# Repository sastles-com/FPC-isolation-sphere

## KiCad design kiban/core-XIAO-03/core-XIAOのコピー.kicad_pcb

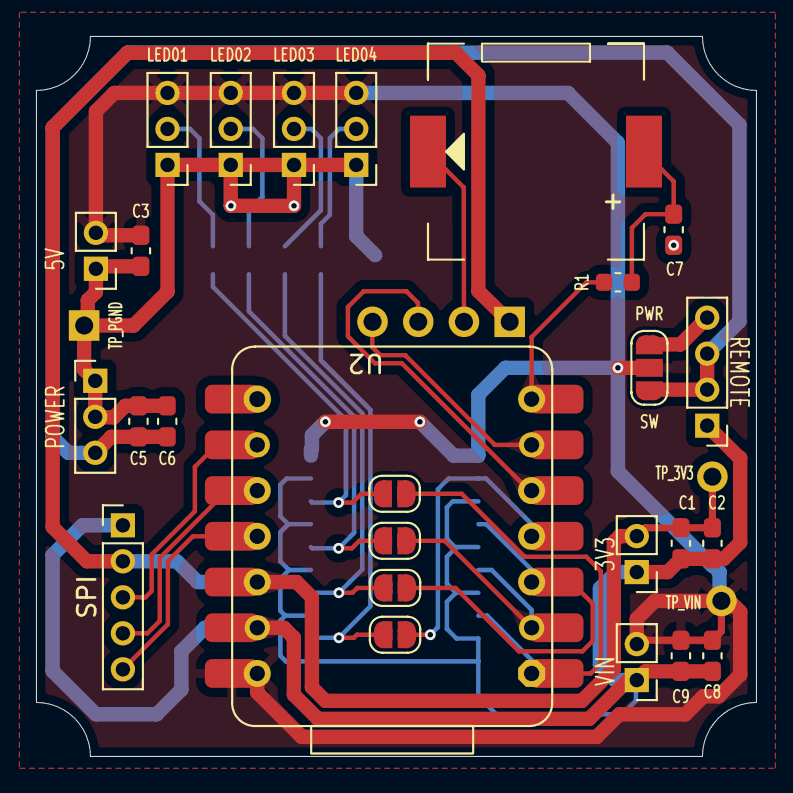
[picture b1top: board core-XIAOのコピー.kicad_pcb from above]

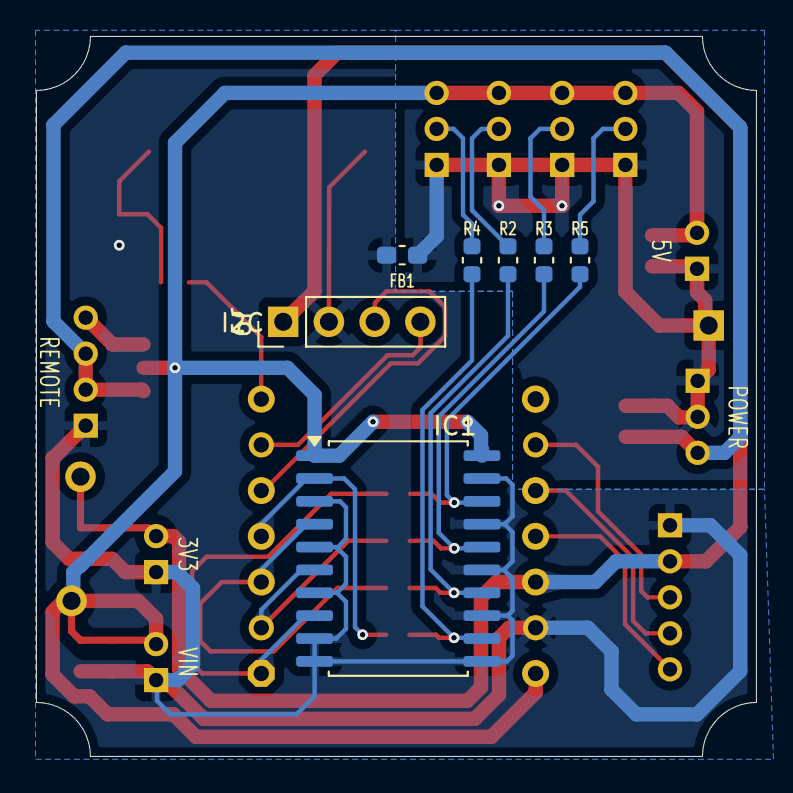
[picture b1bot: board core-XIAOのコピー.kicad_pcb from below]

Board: 2 copper layers, 40.0 x 40.0 mm, 36 parts (7 on the bottom side), 25 nets.

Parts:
C1, C5, C8: 10uF; C_0603_1608Metric_Pad1.08x0.95mm_HandSolder
C2, C3, C6, C7, C9: 0.1uF; C_0603_1608Metric_Pad1.08x0.95mm_HandSolder
FB1: FerriteBead_Small; C_0603_1608Metric_Pad1.08x0.95mm_HandSolder
IC1: 74HCT245; SOIC-20W_7.5x12.8mm_P1.27mm
J1: POWER; PinHeader_1x03_P2.00mm_Vertical
J2: REMOTE; PinHeader_1x04_P2.00mm_Vertical
J3: SPI; PinHeader_1x05_P2.00mm_Vertical
J5: 3V3; PinHeader_1x02_P2.00mm_Vertical
J6: 5V; PinHeader_1x02_P2.00mm_Vertical
J7: LED03; PinHeader_1x03_P2.00mm_Vertical
J8: LED02; PinHeader_1x03_P2.00mm_Vertical
J9: I2C; PinHeader_1x04_P2.54mm_Vertical
J10: LED04; PinHeader_1x03_P2.00mm_Vertical
J11: LED01; PinHeader_1x03_P2.00mm_Vertical
J12: TP_VIN; PinHeader_1x01_P2.54mm_Vertical
J13: TP_3V3; PinHeader_1x01_P2.54mm_Vertical
J14: TP_PGND; PinHeader_1x01_P2.54mm_Vertical
J15: VIN; PinHeader_1x02_P2.00mm_Vertical
JP1: SolderJumper_3_Open; SolderJumper-3_P1.3mm_Open_RoundedPad1.0x1.5mm_NumberLabels
JP2, JP3, JP4, JP5: SolderJumper_2_Open; SolderJumper-2_P1.3mm_Open_RoundedPad1.0x1.5mm
LS1: SPEAKER; speaker-PKLCS1212
R1: 0Ω; C_0603_1608Metric
R2, R3, R4, R5: 33Ω; C_0603_1608Metric
U2: MOUDLE-SEEEDUINO-XIAO-ESP32S3; XIAO-RP2350

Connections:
3V3: C1.1, C2.1, J3.2, J5.2, J9.1, J13.1, U2.12 (3V3)
AGND: C1.2, C2.2, C7.2, C8.2, C9.2, FB1.2, IC1.3 (A2), IC1.5 (A4), IC1.7 (A6), IC1.9 (A8), IC1.10 (GND), IC1.11 (B8), IC1.13 (B6), IC1.15 (B4), IC1.17 (B2), IC1.19 (~OE), J2.1, J3.1, J5.1, J9.2, J15.1, LS1.LEAD-, U2.13 (GND)
GPIO01: IC1.8 (A7), JP2.1 (A), U2.1 (PA02_A0_D0)
GPIO02: IC1.6 (A5), JP3.1 (A), U2.2 (PA4_A1_D1)
GPIO03: IC1.4 (A3), JP4.1 (A), U2.3 (PA10_A2_D2)
GPIO04: IC1.2 (A1), JP5.1 (A), U2.4 (PA11_A3_D3)
GPIO43: R1.1, U2.7 (PB08_A6_TX)
LED01: IC1.18 (B1), JP2.2 (B), R5.2
LED02: IC1.16 (B3), JP3.2 (B), R3.2
LED03: IC1.14 (B5), JP4.2 (B), R2.2
LED04: IC1.12 (B7), JP5.2 (B), R4.2
unnamed: C7.1, LS1.LEAD+, R1.2
unnamed: J2.4, JP1.3 (B)
unnamed: J7.2, R2.1
unnamed: J8.2, R3.1
unnamed: J10.2, R4.1
unnamed: J11.2, R5.1
PGND: C3.2, C5.2, C6.2, FB1.1, J1.1, J1.2, J6.1, J7.1, J8.1, J10.1, J11.1, J14.1
POWER: C5.1, C6.1, J1.3, J2.2, J2.3, JP1.1 (A)
SCL: J9.4, U2.6 (PA9_A5_D5_SCL)
SDA: J9.3, U2.5 (PA8_A4_D4_SDA)
SPI_MISO: J3.4, U2.10 (PA5_A9_D9_MISO)
SPI_MOSI: J3.5, U2.11 (PA6_A10_D10_MOSI)
SPI_SCK: J3.3, U2.9 (PA7_A8_D8_SCK)
VIN: C3.1, C8.1, C9.1, IC1.1 (DIR), IC1.20 (VCC), J6.2, J7.3, J8.3, J10.3, J11.3, J12.1, J15.2, JP1.2 (C), U2.14 (5V)

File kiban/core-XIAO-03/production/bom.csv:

Designator,Footprint,Quantity,Value,LCSC Part #
"C1, C5, C8",0603,3,10uF,
"C2, C3, C6, C7, C9",0603,5,0.1uF,
D1,0603,1,LED,
FB1,0603,1,FerriteBead_Small,
J1,PinHeader_1x03_P2.00mm_Vertical,1,POWER,
J12,PinHeader_1x01_P2.54mm_Vertical,1,TP_VIN,
J13,PinHeader_1x01_P2.54mm_Vertical,1,TP_3V3,
"J14_2, J14",PinHeader_1x01_P2.54mm_Vertical,2,TP_PGND,
J15,PinHeader_1x02_P2.00mm_Vertical,1,VIN,
J2,PinHeader_1x06_P2.54mm_Vertical,1,ESP32-01,
J3,PinHeader_1x05_P2.00mm_Vertical,1,SPI,
J4,PinHeader_1x06_P2.54mm_Vertical,1,ESP32-02,
J5,PinHeader_1x02_P2.00mm_Vertical,1,3V3,
J6,PinHeader_1x02_P2.00mm_Vertical,1,5V,
J9,PinHeader_1x04_P2.54mm_Vertical,1,I2C,
LS1,speaker-PKLCS1212,1,SPEAKER,
R1,0603,1,330Ω,
"R2, R3",0603,2,10kΩ,
U2,XIAO-RP2350,1,MOUDLE-SEEEDUINO-XIAO-ESP32S3,

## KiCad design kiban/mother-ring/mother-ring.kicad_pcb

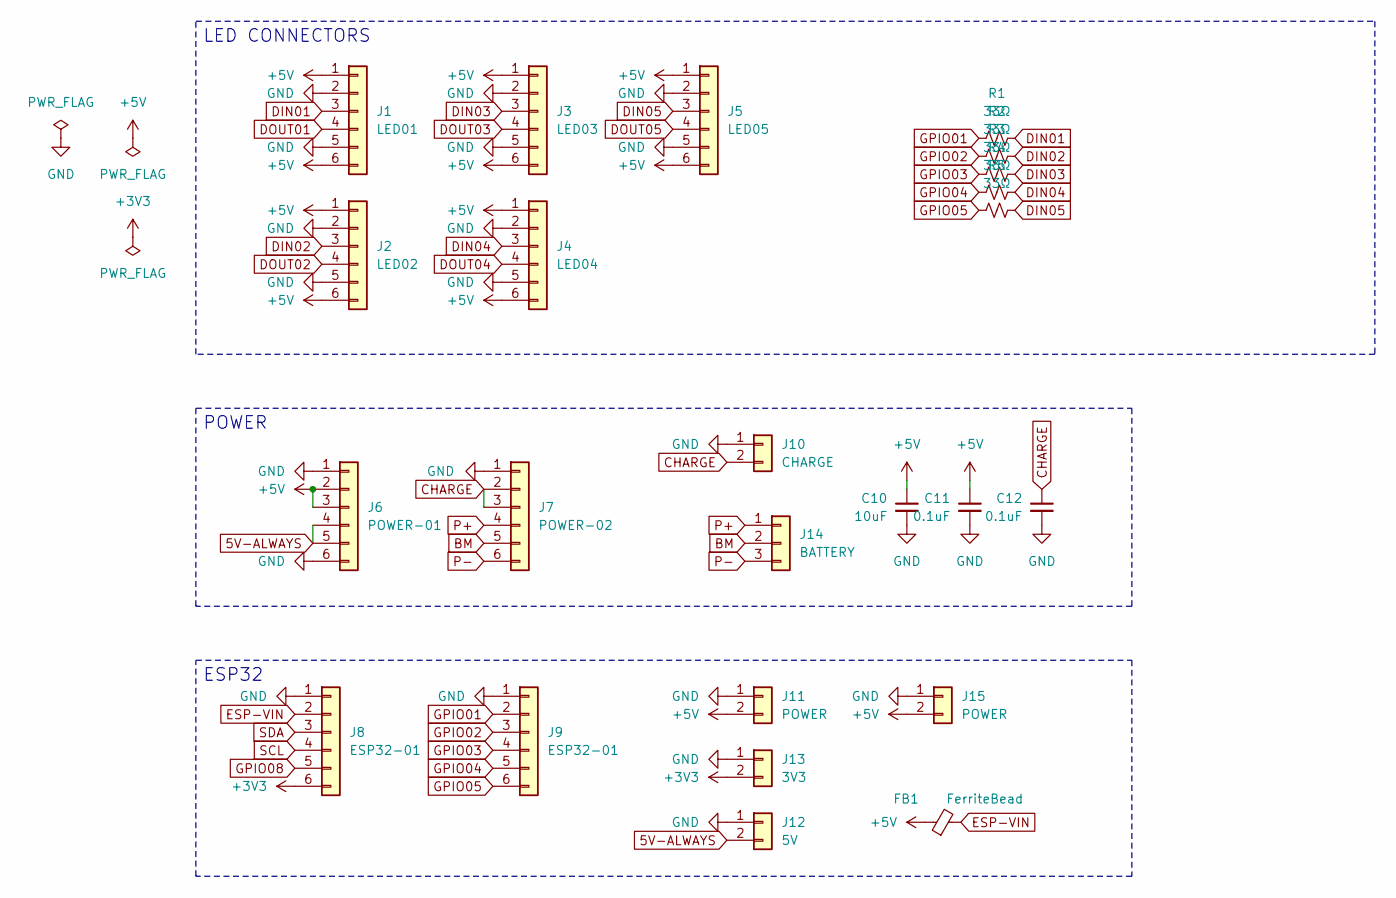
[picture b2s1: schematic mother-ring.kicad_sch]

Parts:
C10: 10uF; C_0603_1608Metric_Pad1.08x0.95mm_HandSolder
C11, C12: 0.1uF; C_0603_1608Metric_Pad1.08x0.95mm_HandSolder
FB1: FerriteBead; L_0603_1608Metric
J1: LED01; pogo-pad 1x06
J2: LED02; pogo-pad 1x06
J3: LED03; pogo-pad 1x06
J4: LED04; pogo-pad 1x06
J5: LED05; pogo-pad 1x06
J6: POWER-01; PinHeader_1x06_P2.54mm_Vertical
J7: POWER-02; PinHeader_1x06_P2.54mm_Vertical
J8, J9: ESP32-01; PinHeader_1x06_P2.54mm_Vertical
J10: CHARGE; PinHeader_1x02_P2.00mm_Vertical
J11, J15: POWER; PinHeader_1x02_P2.00mm_Vertical
J12: 5V; PinHeader_1x02_P2.00mm_Vertical
J13: 3V3; PinHeader_1x02_P2.00mm_Vertical
J14: BATTERY; PinHeader_1x03_P2.00mm_Vertical
R1, R2, R3, R4, R5: 33Ω; R_0603_1608Metric

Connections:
5V-ALWAYS: J6.4, J6.5, J12.2
+3V3: J8.6, J13.2
+5V: C10.1, C11.1, FB1.1, J1.1, J1.6, J2.1, J2.6, J3.1, J3.6, J4.1, J4.6, J5.1, J5.6, J6.2, J6.3, J11.2, J15.2
BM: J7.5, J14.2
CHARGE: C12.1, J7.2, J7.3, J10.2
DIN01: J1.3, R1.2
DIN02: J2.3, R2.2
DIN03: J3.3, R3.2
DIN04: J4.3, R4.2
DIN05: J5.3, R5.2
DOUT01: J1.4
DOUT02: J2.4
DOUT03: J3.4
DOUT04: J4.4
DOUT05: J5.4
ESP-VIN: FB1.2, J8.2
GND: C10.2, C11.2, C12.2, J1.2, J1.5, J2.2, J2.5, J3.2, J3.5, J4.2, J4.5, J5.2, J5.5, J6.1, J6.6, J7.1, J8.1, J9.1, J10.1, J11.1, J12.1, J13.1, J15.1
GPIO01: J9.2, R1.1
GPIO02: J9.3, R2.1
GPIO03: J9.4, R3.1
GPIO04: J9.5, R4.1
GPIO05: J9.6, R5.1
GPIO08: J8.5
P+: J7.4, J14.1
P-: J7.6, J14.3
SCL: J8.4
SDA: J8.3

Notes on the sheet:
POWER
ESP32
LED CONNECTORS

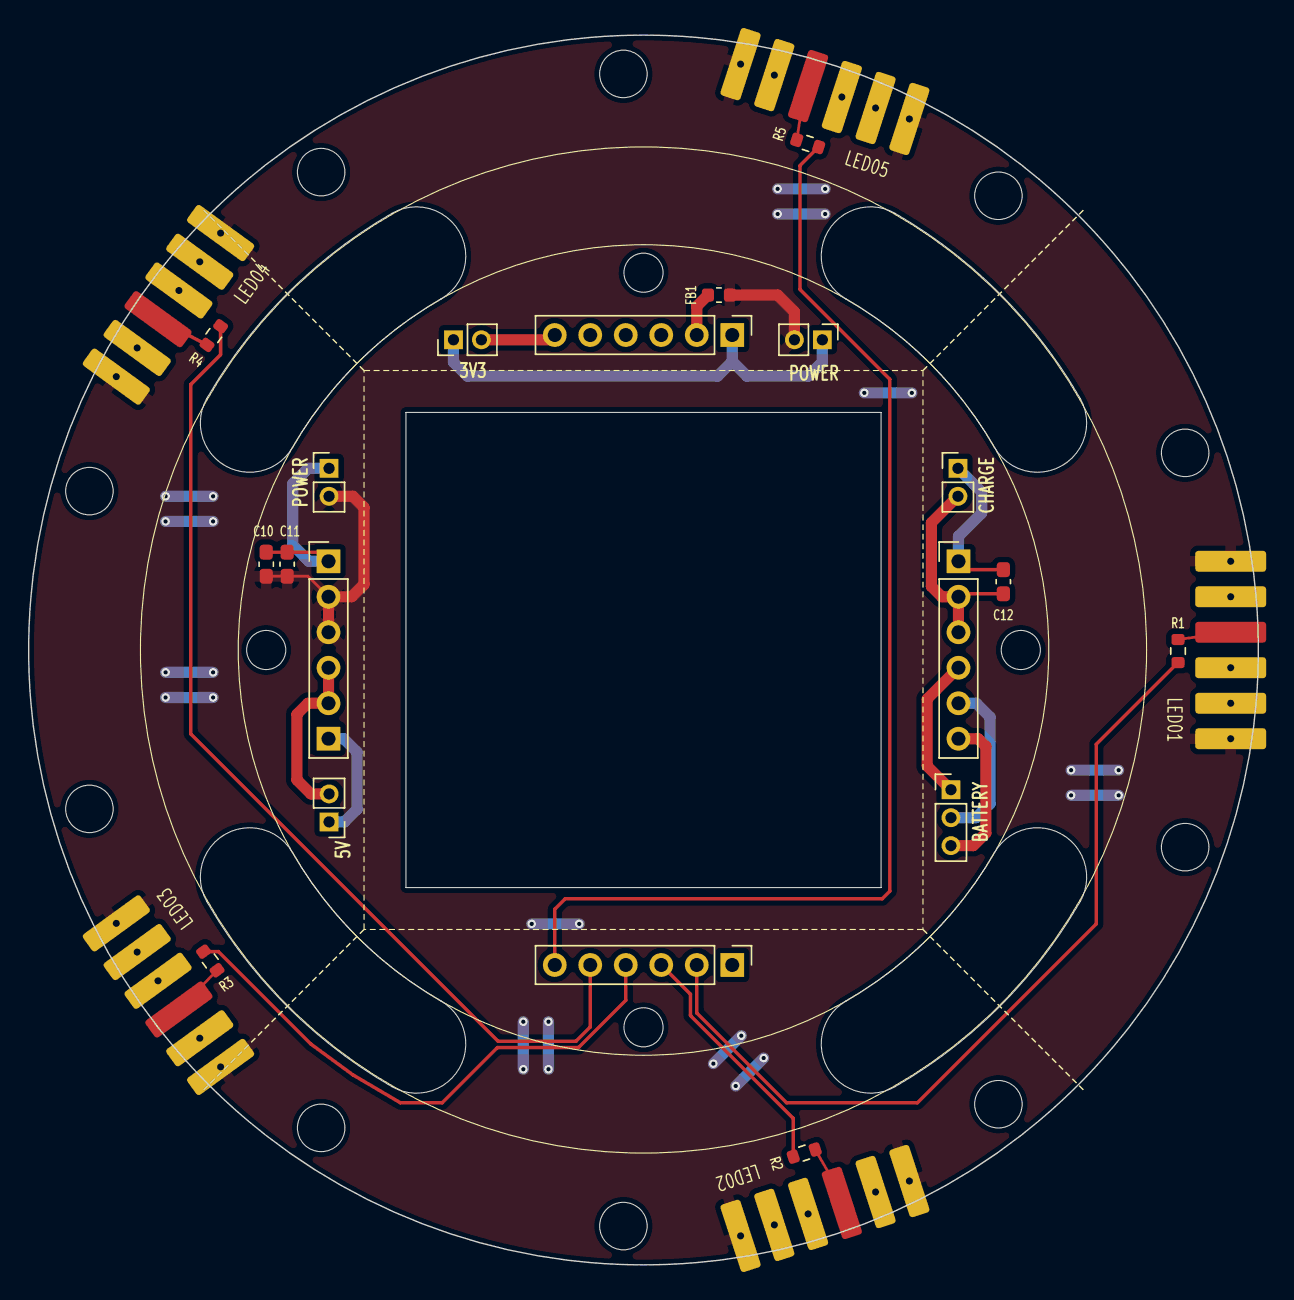
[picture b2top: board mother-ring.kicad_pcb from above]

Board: 2 copper layers, 88.0 x 88.0 mm, 24 parts (0 on the bottom side), 19 nets.

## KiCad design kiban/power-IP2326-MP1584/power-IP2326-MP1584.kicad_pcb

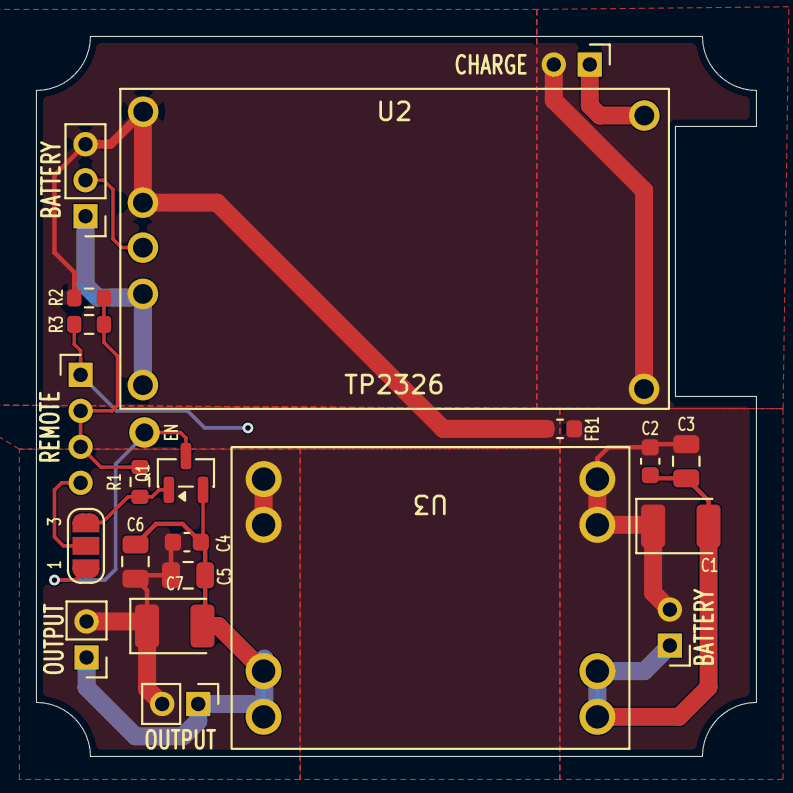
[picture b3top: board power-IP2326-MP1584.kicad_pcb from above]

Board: 2 copper layers, 40.0 x 40.0 mm, 22 parts (0 on the bottom side), 11 nets.

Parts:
C1, C7: 100uF; CP_EIA-3528-12_Kemet-T
C2, C4: 0.1uF; C_0603_1608Metric
C3, C5, C6: 22uF; C_0805_2012Metric
FB1: FerriteBead; L_0603_1608Metric
J2: BATTERY; PinHeader_1x03_P2.00mm_Vertical
J3: BATTERY; PinHeader_1x02_P2.00mm_Vertical
J4, J9: OUTPUT; PinHeader_1x02_P2.00mm_Vertical
J7: REMOTE; PinHeader_1x04_P2.00mm_Vertical
J8: EN; PinHeader_1x01_P2.54mm_TP
J14: CHARGE; PinHeader_1x02_P2.00mm_Vertical
JP1: JUMP; SolderJumper-3_P1.3mm_Open_RoundedPad1.0x1.5mm_NumberLabels
Q1: MMBT3904; SOT-23
R1, R2, R3: 10kΩ; R_0603_1608Metric
U2: TP2326; TS2326
U3: MP1584EN

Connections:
BM: J2.2, U2.2 (BM)
EN: J8.1 (Pin_1_1), JP1.1 (A), Q1.3 (C)
unnamed: JP1.3 (B), Q1.1 (B), R1.1
P+: FB1.1, J2.3, R2.2, U2.1 (B+)
P-: J2.1, U2.3 (B-)
PGND: C1.2, C2.2, C3.2, C4.2, C5.2, C6.2, C7.2, J3.1, J4.1, J7.1, J9.1, J14.1, Q1.2 (E), R3.2, U2.5 (GND), U3.1 (IN-), U3.4 (OUT-)
POUT: J14.2, U2.4 (VIN)
SWITCH: J7.4, JP1.2 (C)
VCC: J7.2, J7.3, R1.2, R2.1, R3.1
VIN: C1.1, C2.1, C3.1, FB1.2, J3.2, U3.2 (IN+)
VOUT: C4.1, C5.1, C6.1, C7.1, J4.2, J9.2, U3.3 (OUT+)

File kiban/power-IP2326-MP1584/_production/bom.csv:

Designator,Footprint,Quantity,Value,LCSC Part #
"C1, C7",CP_EIA-3528-12_Kemet-T,2,100uF,
"C2, C4",0603,2,0.1uF,
"C3, C5, C6",0805,3,22uF,
FB1,0603,1,FerriteBead,
J14,PinHeader_1x02_P2.00mm_Vertical,1,CHARGE,
J2,PinHeader_1x03_P2.00mm_Vertical,1,BATTERY,
J3,PinHeader_1x02_P2.00mm_Vertical,1,BATTERY,
"J4, J9",PinHeader_1x02_P2.00mm_Vertical,2,OUTPUT,
J7,PinHeader_1x04_P2.00mm_Vertical,1,REMOTE,
J8,PinHeader_1x01_P2.54mm_TP,1,EN,
JP1,SolderJumper-3_P1.3mm_Open_RoundedPad1.0x1.5mm_NumberLabels,1,SolderJumper_3_Open,
U2,TS2326,1,TP2326,
U3,MP1584EN,1,MP1584EN,
